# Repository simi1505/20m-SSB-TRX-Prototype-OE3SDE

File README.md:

# 20m-SSB-TRX-Prototype-OE3SDE
Prototype on a 20m SSB TRX for ham radio by OE3SDE.

## Block Diagram

**Figure 1**: Block diagram of 20m SSB TRX.

## Frequency Spectrum

**Figure 2**: Frequency spectrum of 20m SSB TRX.

## Result

**Figure 3**: Result of 20m SSB TRX prototype.

**Figure 4**: Result of 20m SSB TRX prototype.

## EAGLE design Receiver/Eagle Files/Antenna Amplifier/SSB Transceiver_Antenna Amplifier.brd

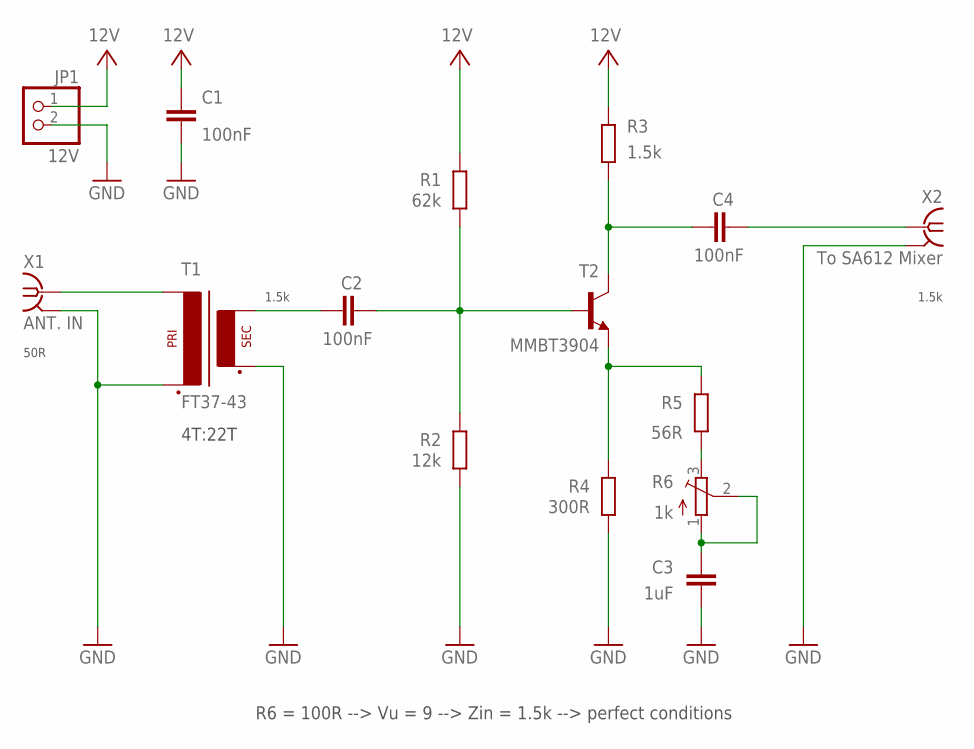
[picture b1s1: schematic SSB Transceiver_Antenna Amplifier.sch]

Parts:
C1, C2, C4: 100nF; C0805
C3: 1uF; C0805
JP1: 12V; 1X02
R1: 62k; R0805
R2: 12k; R0805
R3: 1.5k; R0805
R4: 300R; R0805
R5: 56R; R0805
R6: 1k; 3223G
T1: FT37-43; FT37-43SMD
T2: MMBT3904; SOT23-BEC
X1: ANT. IN; J502-ND-142-0711-821/826
X2: To SA612 Mixer; J502-ND-142-0711-821/826

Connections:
GND: C1.1, C3.1, JP1.2, R2.2, R4.2, T1.P$2 (P2), T1.S$2 (S2), X1.G@1 (2), X1.G@2 (2), X1.G@3 (2), X1.G@4 (2), X2.G@1 (2), X2.G@2 (2), X2.G@3 (2), X2.G@4 (2)
unnamed: R4.1, R5.1, T2.E
unnamed: C3.2, R6.1 (A), R6.2 (S)
unnamed: C4.1, R3.2, T2.C
unnamed: T1.P$1 (P1), X1.1
unnamed: C2.2, R1.2, R2.1, T2.B
unnamed: C4.2, X2.1
unnamed: C2.1, T1.S$1 (S1)
unnamed: R5.2, R6.3 (E)
VCC: C1.2, JP1.1, R1.1, R3.1

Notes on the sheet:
50R
1.5k
4T:22T
R6 = 100R --> Vu = 9 --> Zin = 1.5k --> perfect conditions

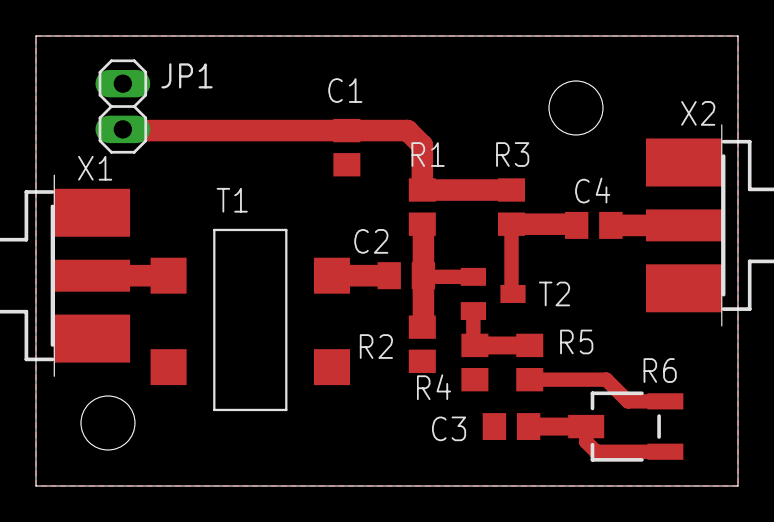
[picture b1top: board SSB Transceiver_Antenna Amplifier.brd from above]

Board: 2 copper layers, 39.0 x 25.0 mm, 15 parts (0 on the bottom side), 10 nets.

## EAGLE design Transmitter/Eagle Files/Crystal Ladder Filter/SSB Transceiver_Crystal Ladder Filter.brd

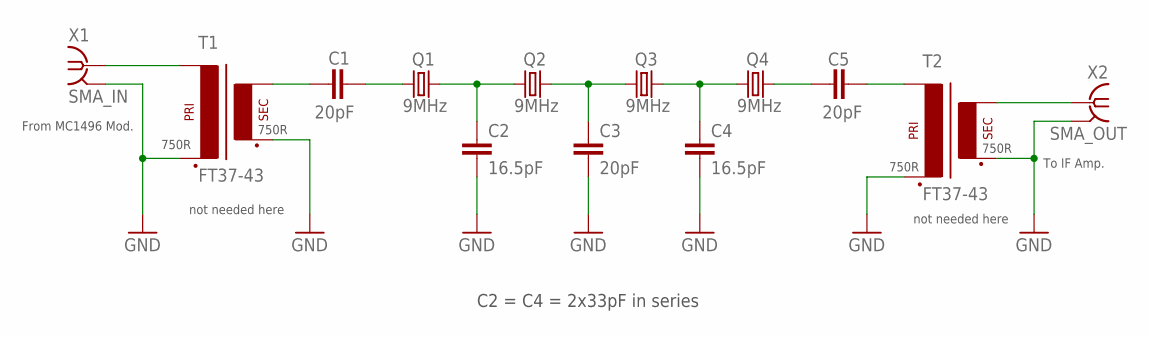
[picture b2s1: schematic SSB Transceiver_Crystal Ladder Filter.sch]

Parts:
C1, C3, C5: 20pF; C0805
C2, C4: 16.5pF; C0805
Q1, Q2, Q3, Q4: 9MHz; HC49/S
T1, T2: FT37-43; FT37-43SMD
X1: SMA_IN; J502-ND-142-0711-821/826
X2: SMA_OUT; J502-ND-142-0711-821/826

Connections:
GND: C2.2, C3.2, C4.2, T1.P$2 (P2), T1.S$2 (S2), T2.P$2 (P2), T2.S$2 (S2), X1.G@1 (2), X1.G@2 (2), X1.G@3 (2), X1.G@4 (2), X2.G@1 (2), X2.G@2 (2), X2.G@3 (2), X2.G@4 (2)
unnamed: C5.2, T2.P$1 (P1)
unnamed: T2.S$1 (S1), X2.1
unnamed: C1.1, T1.S$1 (S1)
unnamed: T1.P$1 (P1), X1.1
unnamed: C1.2, Q1.1
unnamed: C2.1, Q1.2, Q2.1
unnamed: C3.1, Q2.2, Q3.1
unnamed: C4.1, Q3.2, Q4.1
unnamed: C5.1, Q4.2

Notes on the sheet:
not needed here
750R
C2 = C4 = 2x33pF in series
From MC1496 Mod.
To IF Amp.

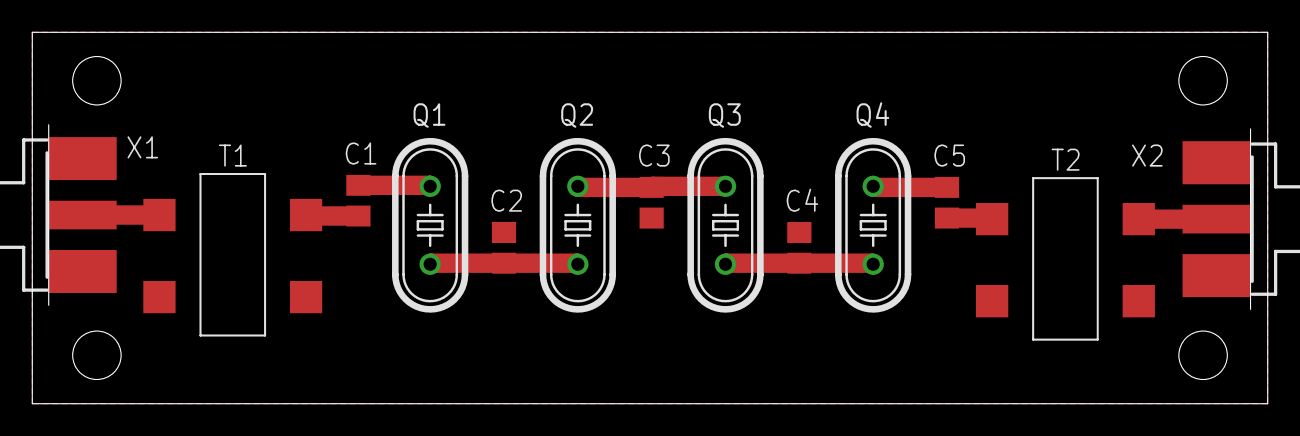
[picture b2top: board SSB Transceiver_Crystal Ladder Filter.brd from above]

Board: 2 copper layers, 76.5 x 23.0 mm, 13 parts (0 on the bottom side), 10 nets.

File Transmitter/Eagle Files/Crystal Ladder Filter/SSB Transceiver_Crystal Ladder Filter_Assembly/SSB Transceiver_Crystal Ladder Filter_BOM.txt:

Partlist exported from E:/Simon Dorrer/DIY Projekte/Amateurfunkprojekte/SSB Transceiver/Transmitter/Eagle Files/Crystal Ladder Filter/SSB Transceiver_Crystal Ladder Filter.sch at 13/01/2020 09:06

Qty Value   Device               Package                  Parts          Description                                           MF                 MPN          OC_FARNELL OC_NEWARK POPULARITY SPICEPREFIX
2   16.5pF  C-EUC0805            C0805                    C2, C4         CAPACITOR, European symbol                                                                                 88         C          
3   20pF    C-EUC0805            C0805                    C1, C3, C5     CAPACITOR, European symbol                                                                                 88         C          
4   9MHz    CRYSTALHC49S         HC49/S                   Q1, Q2, Q3, Q4 CRYSTAL                                                                               1667008    unknown                         
2   FT37-43 FT37-43              FT37-43SMD               T1, T2                                                                                                                                          
1   SMA_IN  SMA-142-0711-821/826 J502-ND-142-0711-821/826 X1             SMA 50 Ohm End Launch Jack Receptacle - Round Contact JOHNSON COMPONENTS 142-0711-821 1019328    16F3627                         
1   SMA_OUT SMA-142-0711-821/826 J502-ND-142-0711-821/826 X2             SMA 50 Ohm End Launch Jack Receptacle - Round Contact JOHNSON COMPONENTS 142-0711-821 1019328    16F3627

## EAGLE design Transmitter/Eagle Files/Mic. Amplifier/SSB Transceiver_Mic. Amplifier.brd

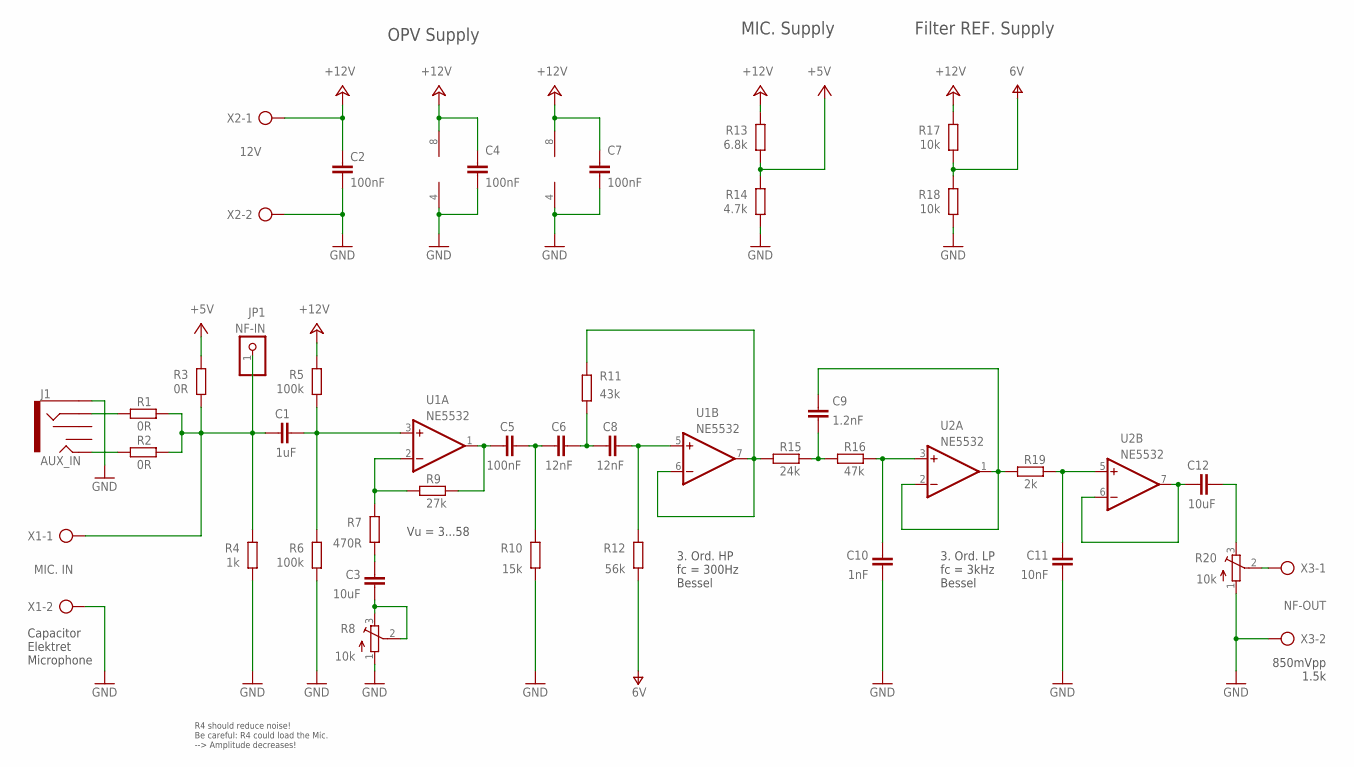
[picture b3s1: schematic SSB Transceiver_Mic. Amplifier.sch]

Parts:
C1: 1uF; C0805
C2, C4, C5, C7: 100nF; C0805
C3, C12: 10uF; C0805
C6, C8: 12nF; C0805
C9: 1.2nF; C0805
C10: 1nF; C0805
C11: 10nF; C0805
J1: AUX_IN; AUDIO-JACK
JP1: NF-IN; 1X01
R1, R2, R3: 0R; R0805
R4: 1k; R0805
R5, R6: 100k; R0805
R7: 470R; R0805
R8, R20: 10k; 3223G
R9: 27k; R0805
R10: 15k; R0805
R11: 43k; R0805
R12: 56k; R0805
R13: 6.8k; R0805
R14: 4.7k; R0805
R15: 24k; R0805
R16: 47k; R0805
R17, R18: 10k; R0805
R19: 2k; R0805
U1, U2: NE5532; SO08
X1: MIC. IN; AK550/2
X2: 12V; AK550/2
X3: NF-OUT; AK550/2

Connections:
+5V: R3.1, R13.2, R14.1
+24V: C2.2, C4.2, C7.2, R5.1, R13.1, R17.1, U1.8 (V+), U2.8 (V+), X2.1
GND: C2.1, C4.1, C7.1, C10.1, C11.1, J1.SLEEVE, R4.2, R6.2, R8.1 (A), R10.2, R14.2, R18.2, R20.1 (A), U1.4 (V-), U2.4 (V-), X1.2, X2.2, X3.2
unnamed: J1.RING, R1.2
unnamed: J1.TIP, R2.2
unnamed: R7.1, R9.1, U1.2 (-IN)
unnamed: C1.1, JP1.1, R1.1, R2.1, R3.2, R4.1, X1.1
unnamed: C1.2, R5.2, R6.1, U1.3 (+IN)
unnamed: C3.2, R7.2
unnamed: C3.1, R8.2 (S), R8.3 (E)
unnamed: C5.1, R9.2, U1.1 (OUT)
unnamed: C5.2, C6.1, R10.1
unnamed: C12.1, U2.6 (-IN), U2.7 (OUT)
unnamed: R20.2 (S), X3.1
unnamed: C12.2, R20.3 (E)
unnamed: R11.1, R15.2, U1.6 (-IN), U1.7 (OUT)
unnamed: C6.2, C8.1, R11.2
unnamed: C8.2, R12.1, U1.5 (+IN)
unnamed: C9.1, R15.1, R16.2
unnamed: C10.2, R16.1, U2.3 (+IN)
unnamed: C9.2, R19.2, U2.1 (OUT), U2.2 (-IN)
unnamed: C11.2, R19.1, U2.5 (+IN)
V+: R12.2, R17.2, R18.1

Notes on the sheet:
Capacitor Elektret Microphone
OPV Supply
MIC. Supply
Filter REF. Supply
Vu = 3...58
3. Ord. HP fc = 300Hz Bessel
3. Ord. LP fc = 3kHz Bessel
850mVpp 1.5k
R4 should reduce noise! Be careful: R4 could load the Mic. --> Amplitude decreases!

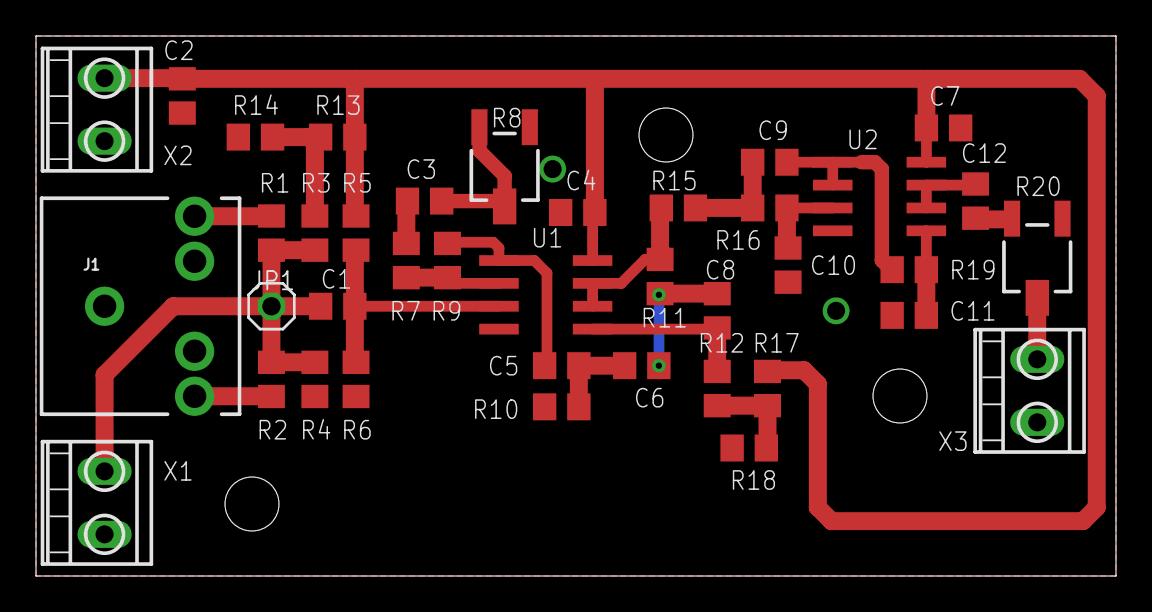
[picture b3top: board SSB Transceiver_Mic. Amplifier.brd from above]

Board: 2 copper layers, 60.0 x 30.0 mm, 39 parts (0 on the bottom side), 23 nets.

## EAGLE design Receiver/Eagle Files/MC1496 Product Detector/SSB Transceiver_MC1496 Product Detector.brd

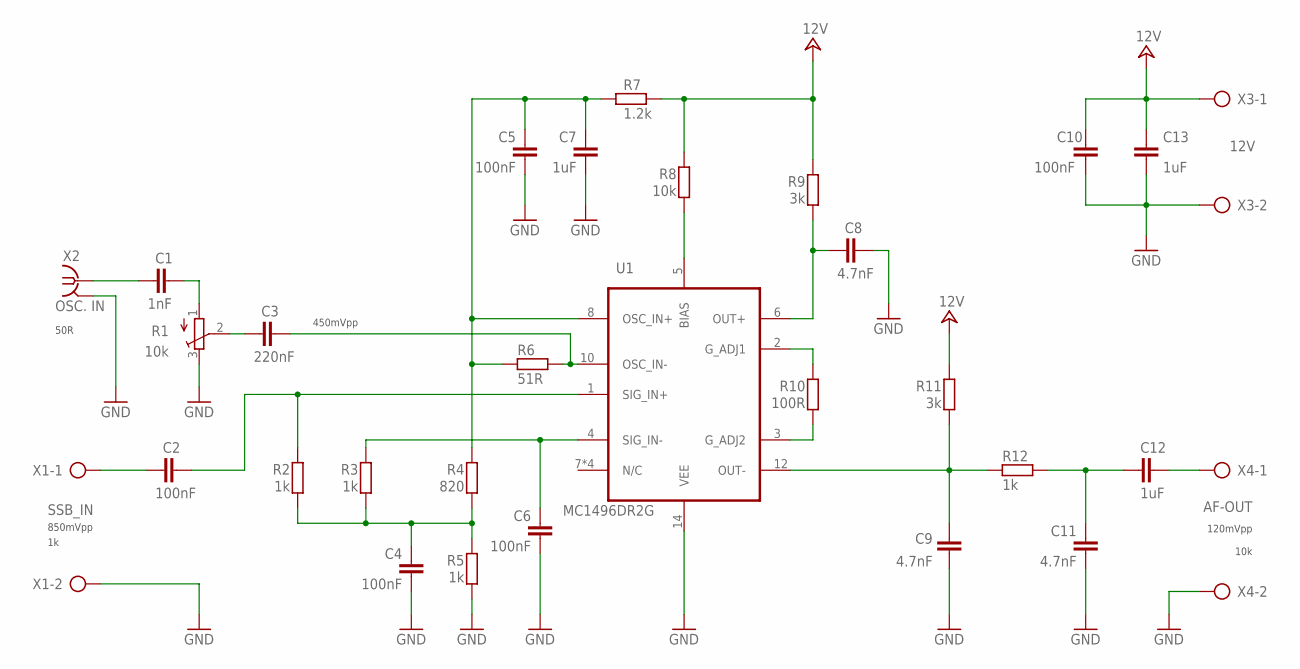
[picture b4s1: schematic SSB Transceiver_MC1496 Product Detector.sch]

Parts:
C1: 1nF; C0805
C2, C4, C5, C6, C10: 100nF; C0805
C3: 220nF; C0805
C7, C12, C13: 1uF; C0805
C8, C9, C11: 4.7nF; C0805
R1: 10k; 3223G
R2, R3, R5, R12: 1k; R0805
R4: 820; R0805
R6: 51R; R0805
R7: 1.2k; R0805
R8: 10k; R0805
R9, R11: 3k; R0805
R10: 100R; R0805
U1: MC1496DR2G; SOIC127P600X175-14N
X1: SSB_IN; AK300/2
X2: OSC. IN; J502-ND-142-0711-821/826
X3: 12V; AK300/2
X4: AF-OUT; AK300/2

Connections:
+24V: C10.2, C13.2, R7.2, R8.1, R9.1, R11.1, X3.1
GND: C4.1, C5.1, C6.1, C7.1, C8.1, C9.1, C10.1, C11.1, C13.1, R1.3 (E), R5.1, U1.14 (VEE), X1.2, X2.G@1 (2), X2.G@2 (2), X2.G@3 (2), X2.G@4 (2), X3.2, X4.2
unnamed: C1.1, X2.1
unnamed: C12.2, X4.1
unnamed: C1.2, R1.1 (A)
unnamed: C3.1, R1.2 (S)
unnamed: C8.2, R9.2, U1.6 (OUT+)
unnamed: C9.2, R11.2, R12.1, U1.12 (OUT-)
unnamed: C11.2, C12.1, R12.2
unnamed: R10.2, U1.3 (G_ADJ2)
unnamed: R10.1, U1.2 (G_ADJ1)
unnamed: C3.2, R6.2, U1.10 (OSC_IN-)
unnamed: R8.2, U1.5 (BIAS)
unnamed: C6.2, R3.1, U1.4 (SIG_IN-)
unnamed: C2.2, R2.2, U1.1 (SIG_IN+)
unnamed: C4.2, R2.1, R3.2, R4.1, R5.2
unnamed: C2.1, X1.1
unnamed: C5.2, C7.2, R4.2, R6.1, R7.1, U1.8 (OSC_IN+)

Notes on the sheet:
10k
120mVpp
50R
450mVpp
850mVpp

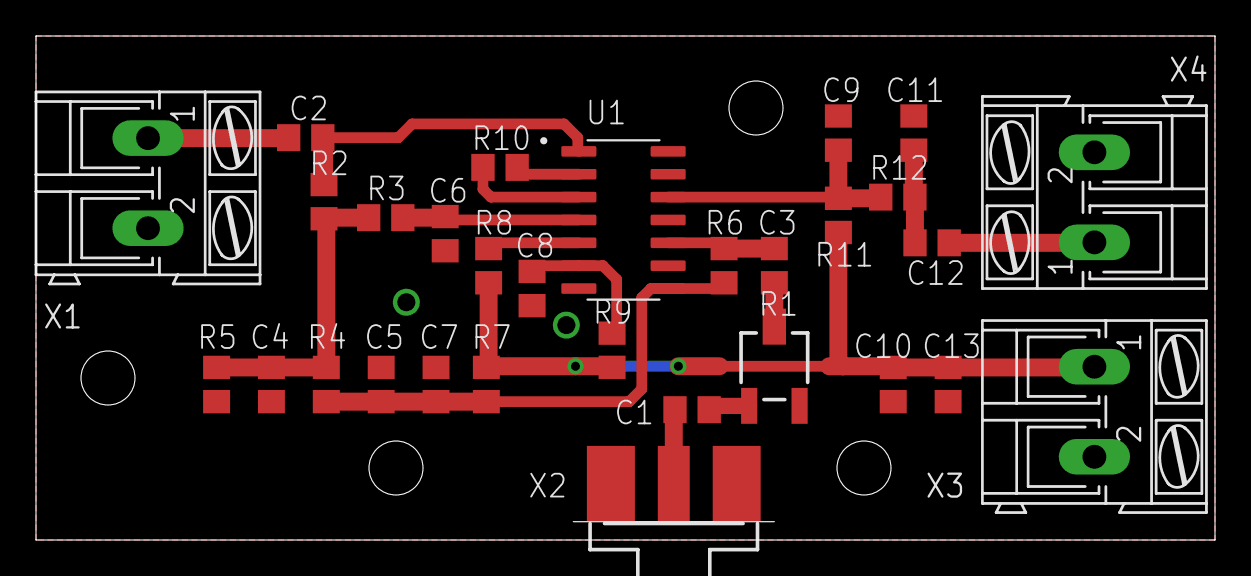
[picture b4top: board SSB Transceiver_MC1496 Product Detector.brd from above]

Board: 2 copper layers, 65.5 x 28.0 mm, 30 parts (0 on the bottom side), 18 nets.

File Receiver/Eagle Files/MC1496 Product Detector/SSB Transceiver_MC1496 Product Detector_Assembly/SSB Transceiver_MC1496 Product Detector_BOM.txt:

Partlist exported from E:/Simon Dorrer/DIY Projekte/Amateurfunkprojekte/SSB Transceiver/Receiver/Eagle Files/MC1496 Product Detector/SSB Transceiver_MC1496 Product Detector.sch at 12/01/2020 20:46

Qty Value      Device               Package                  Parts               Description                                           AVAILABILITY DESCRIPTION                                     MF                 MP         MPN          OC_FARNELL OC_NEWARK PACKAGE                  POPULARITY PRICE SPICEPREFIX
1   1.2k       R-EU_R0805           R0805                    R7                  RESISTOR, European symbol                                                                                                                                                                                   86               R          
1   100R       R-EU_R0805           R0805                    R10                 RESISTOR, European symbol                                                                                                                                                                                   86               R          
5   100nF      C-EUC0805            C0805                    C2, C4, C5, C6, C10 CAPACITOR, European symbol                                                                                                                                                                                  88               C          
1   10k        R-EU_R0805           R0805                    R8                  RESISTOR, European symbol                                                                                                                                                                                   86               R          
1   10k        TRIM_EU-3223G        3223G                    R1                  POTENTIOMETER                                                                                                                                                                                                                           
1   12V        AK300/2              AK300/2                  X3                  CONNECTOR                                                                                                                                                     unknown    unknown                                                        
4   1k         R-EU_R0805           R0805                    R2, R3, R5, R12     RESISTOR, European symbol                                                                                                                                                                                   86               R          
1   1nF        C-EUC0805            C0805                    C1                  CAPACITOR, European symbol                                                                                                                                                                                  88               C          
3   1uF        C-EUC0805            C0805                    C7, C12, C13        CAPACITOR, European symbol                                                                                                                                                                                  88               C          
1   220nF      C-EUC0805            C0805                    C3                  CAPACITOR, European symbol                                                                                                                                                                                  88               C          
2   3k         R-EU_R0805           R0805                    R9, R11             RESISTOR, European symbol                                                                                                                                                                                   86               R          
3   4.7nF      C-EUC0805            C0805                    C8, C9, C11         CAPACITOR, European symbol                                                                                                                                                                                  88               C          
1   51R        R-EU_R0805           R0805                    R6                  RESISTOR, European symbol                                                                                                                                                                                   86               R          
1   820        R-EU_R0805           R0805                    R4                  RESISTOR, European symbol                                                                                                                                                                                   86               R          
1   AF-OUT     AK300/2              AK300/2                  X4                  CONNECTOR                                                                                                                                                     unknown    unknown                                                        
1   MC1496DR2G MC1496DR2G           SOIC127P600X175-14N      U1                                                                        Unavailable   RF IC Modulator/Demodulator FM 300MHz 14-SOIC  ON Semiconductor   MC1496DR2G                                   SOIC-14 ON Semiconductor            None             
1   OSC. IN    SMA-142-0711-821/826 J502-ND-142-0711-821/826 X2                  SMA 50 Ohm End Launch Jack Receptacle - Round Contact                                                              JOHNSON COMPONENTS            142-0711-821 1019328    16F3627                                                        
1   SSB_IN     AK300/2              AK300/2                  X1                  CONNECTOR                                                                                                                                                     unknown    unknown

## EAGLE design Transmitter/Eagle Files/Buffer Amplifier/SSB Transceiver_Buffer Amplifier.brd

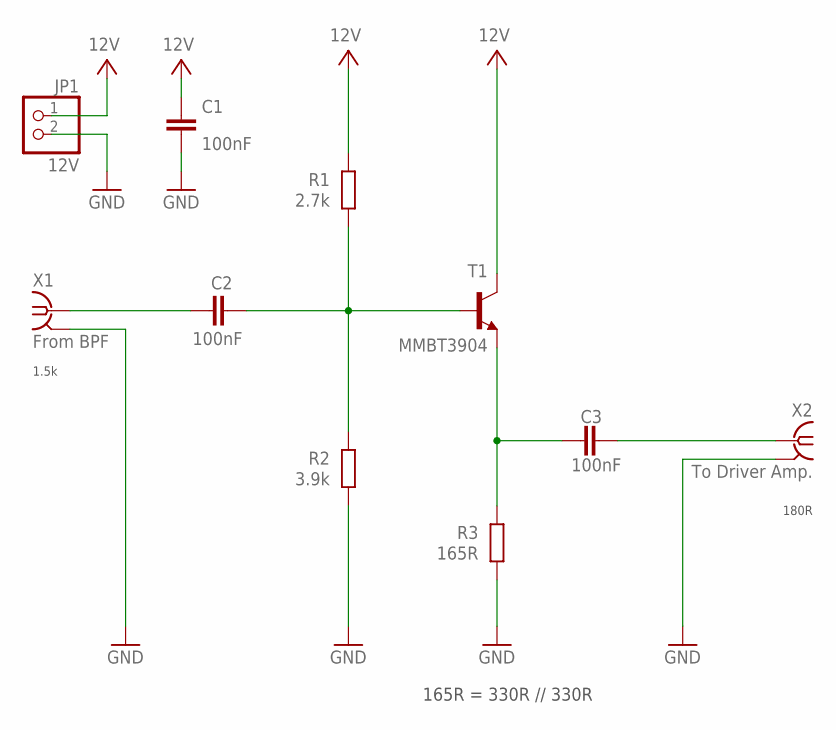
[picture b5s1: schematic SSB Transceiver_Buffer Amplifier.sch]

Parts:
C1, C2, C3: 100nF; C0805
JP1: 12V; 1X02
R1: 2.7k; R0805
R2: 3.9k; R0805
R3: 165R; R0805
T1: MMBT3904; SOT23-BEC
X1: From BPF; J502-ND-142-0711-821/826
X2: To Driver Amp.; J502-ND-142-0711-821/826

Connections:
GND: C1.1, JP1.2, R2.2, R3.2, X1.G@1 (GND), X1.G@2 (GND), X1.G@3 (GND), X1.G@4 (GND), X2.G@1 (GND), X2.G@2 (GND), X2.G@3 (GND), X2.G@4 (GND)
unnamed: C3.2, R3.1, T1.E
unnamed: C3.1, X2.1 (RF)
unnamed: C2.2, R1.2, R2.1, T1.B
unnamed: C2.1, X1.1 (RF)
VCC: C1.2, JP1.1, R1.1, T1.C

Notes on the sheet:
1.5k
180R
165R = 330R // 330R

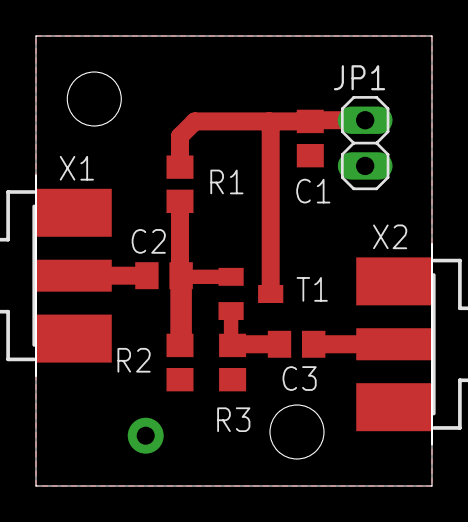
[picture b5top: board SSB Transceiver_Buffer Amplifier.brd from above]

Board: 2 copper layers, 22.0 x 25.0 mm, 10 parts (0 on the bottom side), 6 nets.

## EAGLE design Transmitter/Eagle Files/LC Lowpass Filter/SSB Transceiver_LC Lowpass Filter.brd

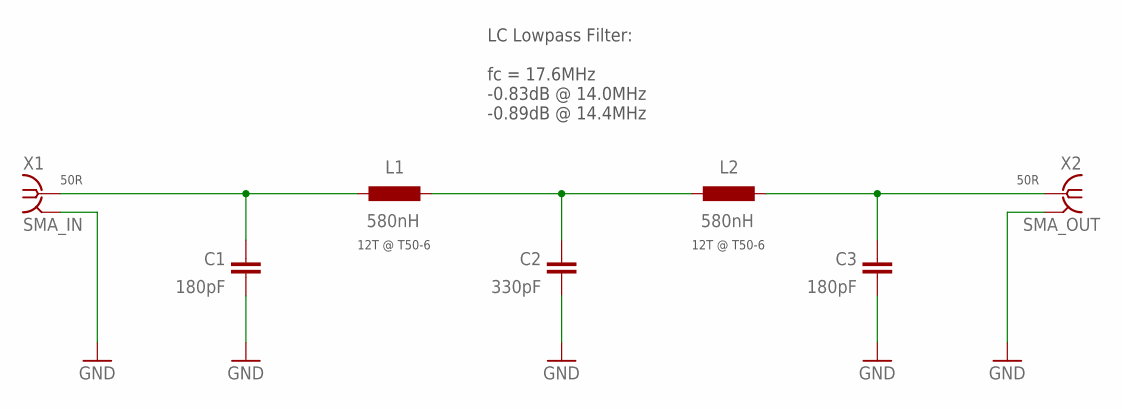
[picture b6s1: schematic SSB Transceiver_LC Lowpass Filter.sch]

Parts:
C1, C3: 180pF; C0805
C2: 330pF; C0805
L1, L2: 580nH; T50-6SMD
X1: SMA_IN; J502-ND-142-0711-821/826
X2: SMA_OUT; J502-ND-142-0711-821/826

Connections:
GND: C1.1, C2.1, C3.1, X1.G@1 (2), X1.G@2 (2), X1.G@3 (2), X1.G@4 (2), X2.G@1 (2), X2.G@2 (2), X2.G@3 (2), X2.G@4 (2)
unnamed: C2.2, L1.P$2 (2), L2.P$1 (1)
unnamed: C3.2, L2.P$2 (2), X2.1
unnamed: C1.2, L1.P$1 (1), X1.1

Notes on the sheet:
50R
LC Lowpass Filter: fc = 17.6MHz -0.83dB @ 14.0MHz -0.89dB @ 14.4MHz
12T @ T50-6

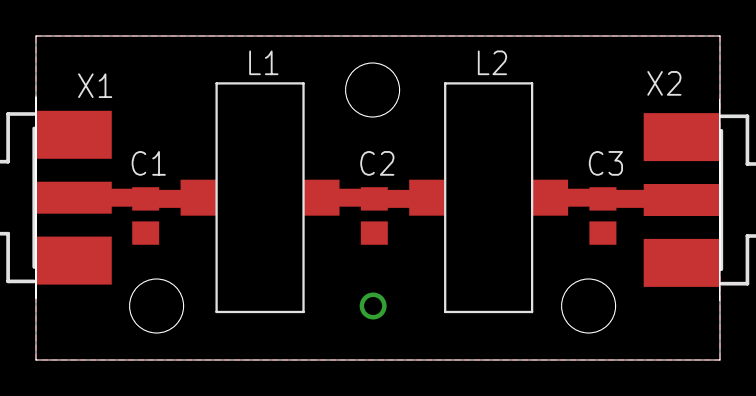
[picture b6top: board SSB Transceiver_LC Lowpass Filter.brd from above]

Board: 2 copper layers, 38.0 x 18.0 mm, 7 parts (0 on the bottom side), 4 nets.

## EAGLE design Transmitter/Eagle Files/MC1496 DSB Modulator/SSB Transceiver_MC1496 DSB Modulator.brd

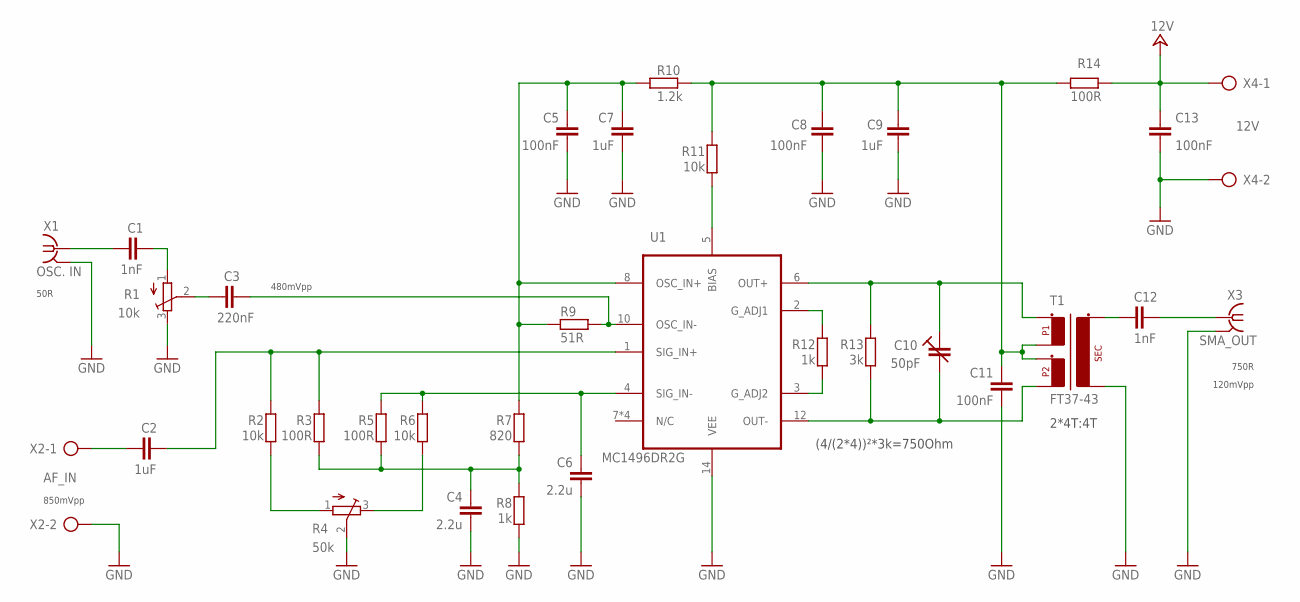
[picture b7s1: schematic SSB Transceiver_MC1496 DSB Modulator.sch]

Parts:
C1, C12: 1nF; C0805
C2, C7, C9: 1uF; C0805
C3: 220nF; C0805
C4, C6: 2.2u; C0805
C5, C8, C11, C13: 100nF; C0805
C10: 50pF; VARIABLECAP-SMD
R1: 10k; 3223G
R2, R6, R11: 10k; R0805
R3, R5, R14: 100R; R0805
R4: 50k; 3223G
R7: 820; R0805
R8, R12: 1k; R0805
R9: 51R; R0805
R10: 1.2k; R0805
R13: 3k; R0805
T1: FT37-43; FT37-43CENTERTAPSMD
U1: MC1496DR2G; SOIC127P600X175-14N
X1: OSC. IN; J502-ND-142-0711-821/826
X2: AF_IN; AK300/2
X3: SMA_OUT; J502-ND-142-0711-821/826
X4: 12V; AK300/2

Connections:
+24V: C13.2, R14.2, X4.1
GND: C4.1, C5.1, C6.1, C7.1, C8.1, C9.1, C11.1, C13.1, R1.3 (E), R4.2 (S), R8.1, T1.S$2 (S2), U1.14 (VEE), X1.G@1 (2), X1.G@2 (2), X1.G@3 (2), X1.G@4 (2), X2.2, X3.G@1 (2), X3.G@2 (2), X3.G@3 (2), X3.G@4 (2), X4.2
unnamed: C1.1, X1.1
unnamed: C12.2, X3.1
unnamed: C1.2, R1.1 (A)
unnamed: C3.1, R1.2 (S)
unnamed: C8.2, C9.2, C11.2, R10.2, R11.1, R14.1, T1.P$2 (P1_2), T1.P$3 (P2_1)
unnamed: C12.1, T1.S$1 (S1)
unnamed: C10.P$1 (E), R13.1, T1.P$1 (P1_1), U1.6 (OUT+)
unnamed: C10.P$2 (A), R13.2, T1.P$4 (P2_2), U1.12 (OUT-)
unnamed: R12.2, U1.3 (G_ADJ2)
unnamed: R12.1, U1.2 (G_ADJ1)
unnamed: C3.2, R9.2, U1.10 (OSC_IN-)
unnamed: R11.2, U1.5 (BIAS)
unnamed: R2.1, R4.1 (A)
unnamed: R4.3 (E), R6.2
unnamed: C6.2, R5.2, R6.1, U1.4 (SIG_IN-)
unnamed: C2.2, R2.2, R3.2, U1.1 (SIG_IN+)
unnamed: C4.2, R3.1, R5.1, R7.1, R8.2
unnamed: C2.1, X2.1
unnamed: C5.2, C7.2, R7.2, R9.1, R10.1, U1.8 (OSC_IN+)

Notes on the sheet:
750R
120mVpp
50R
480mVpp
850mVpp
(4/(2*4))²*3k=750Ohm
2*4T:4T

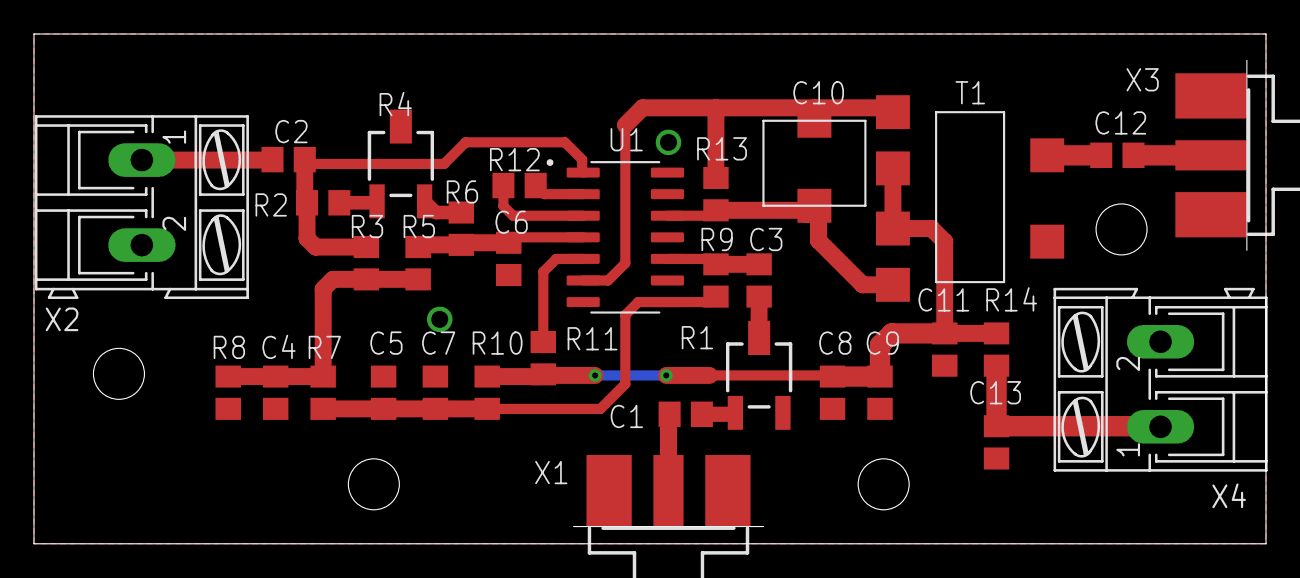
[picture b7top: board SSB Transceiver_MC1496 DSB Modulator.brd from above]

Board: 2 copper layers, 72.5 x 30.0 mm, 33 parts (0 on the bottom side), 21 nets.

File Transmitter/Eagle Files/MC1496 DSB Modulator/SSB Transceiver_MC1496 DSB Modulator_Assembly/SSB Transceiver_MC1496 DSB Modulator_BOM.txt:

Partlist exported from E:/Simon Dorrer/DIY Projekte/Amateurfunkprojekte/SSB Transceiver/Transmitter/Eagle Files/MC1496 DSB Modulator/SSB Transceiver_MC1496 DSB Modulator.sch at 12/01/2020 14:15

Qty Value      Device               Package                  Parts            Description                                           AVAILABILITY DESCRIPTION                                     MF                 MP         MPN          OC_FARNELL OC_NEWARK PACKAGE                  POPULARITY PRICE SPICEPREFIX
1   1.2k       R-EU_R0805           R0805                    R10              RESISTOR, European symbol                                                                                                                                                                                   86               R          
3   100R       R-EU_R0805           R0805                    R3, R5, R14      RESISTOR, European symbol                                                                                                                                                                                   86               R          
4   100nF      C-EUC0805            C0805                    C5, C8, C11, C13 CAPACITOR, European symbol                                                                                                                                                                                  88               C          
3   10k        R-EU_R0805           R0805                    R2, R6, R11      RESISTOR, European symbol                                                                                                                                                                                   86               R          
1   10k        TRIM_EU-3223G        3223G                    R1               POTENTIOMETER                                                                                                                                                                                                                           
1   12V        AK300/2              AK300/2                  X4               CONNECTOR                                                                                                                                                     unknown    unknown                                                        
2   1k         R-EU_R0805           R0805                    R8, R12          RESISTOR, European symbol                                                                                                                                                                                   86               R          
2   1nF        C-EUC0805            C0805                    C1, C12          CAPACITOR, European symbol                                                                                                                                                                                  88               C          
3   1uF        C-EUC0805            C0805                    C2, C7, C9       CAPACITOR, European symbol                                                                                                                                                                                  88               C          
2   2.2u       C-EUC0805            C0805                    C4, C6           CAPACITOR, European symbol                                                                                                                                                                                  88               C          
1   220nF      C-EUC0805            C0805                    C3               CAPACITOR, European symbol                                                                                                                                                                                  88               C          
1   3k       R-EU_R0805           R0805                    R13              RESISTOR, European symbol                                                                                                                                                                                   86               R          
1   50k        TRIM_EU-3223G        3223G                    R4               POTENTIOMETER                                                                                                                                                                                                                           
1   50pF       VARIABLECAP          VARIABLECAP-SMD          C10                                                                                                                                                                                                                                                      
1   51R        R-EU_R0805           R0805                    R9               RESISTOR, European symbol                                                                                                                                                                                   86               R          
1   820        R-EU_R0805           R0805                    R7               RESISTOR, European symbol                                                                                                                                                                                   86               R          
1   AF_IN      AK300/2              AK300/2                  X2               CONNECTOR                                                                                                                                                     unknown    unknown                                                        
1   FT37-43    FT37-43CENTERTAP     FT37-43CENTERTAPSMD      T1                                                                                                                                                                                                                                                       
1   MC1496DR2G MC1496DR2G           SOIC127P600X175-14N      U1                                                                     Unavailable   RF IC Modulator/Demodulator FM 300MHz 14-SOIC  ON Semiconductor   MC1496DR2G                                   SOIC-14 ON Semiconductor            None             
1   OSC. IN    SMA-142-0711-821/826 J502-ND-142-0711-821/826 X1               SMA 50 Ohm End Launch Jack Receptacle - Round Contact                                                              JOHNSON COMPONENTS            142-0711-821 1019328    16F3627                                                        
1   SMA_OUT    SMA-142-0711-821/826 J502-ND-142-0711-821/826 X3               SMA 50 Ohm End Launch Jack Receptacle - Round Contact                                                              JOHNSON COMPONENTS            142-0711-821 1019328    16F3627

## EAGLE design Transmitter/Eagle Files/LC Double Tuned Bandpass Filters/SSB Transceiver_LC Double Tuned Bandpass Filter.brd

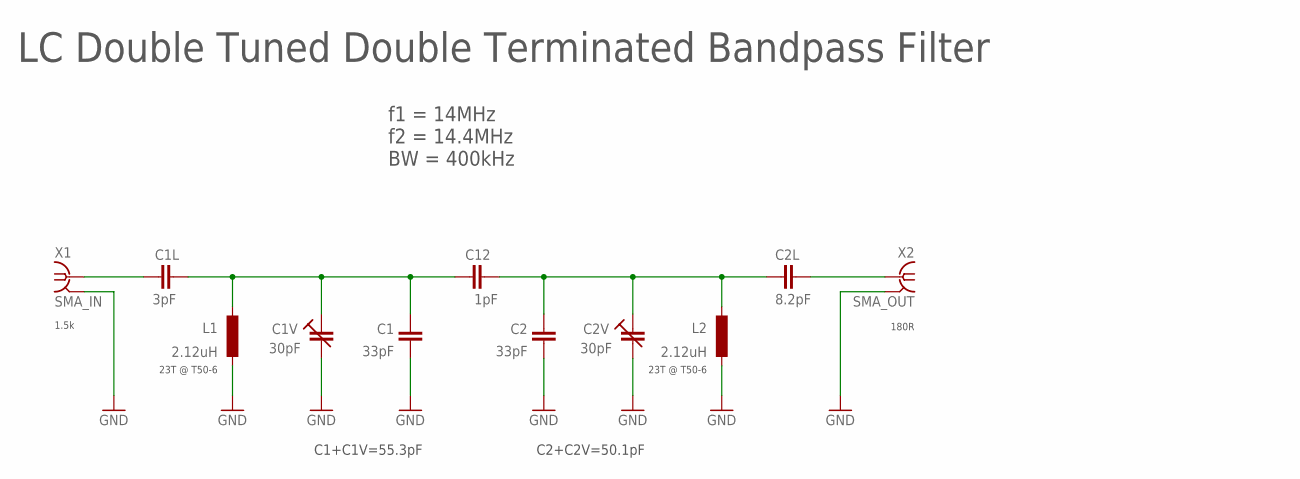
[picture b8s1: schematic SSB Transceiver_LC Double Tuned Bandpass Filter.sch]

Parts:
C1, C2: 33pF; C0805
C1L: 3pF; C0805
C1V, C2V: 30pF; VARIABLECAP-SMD
C2L: 8.2pF; C0805
C12: 1pF; C0805
L1, L2: 2.12uH; T50-6SMD
X1: SMA_IN; J502-ND-142-0711-821/826
X2: SMA_OUT; J502-ND-142-0711-821/826

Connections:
GND: C1.1, C1V.P$2 (A), C2.1, C2V.P$2 (A), L1.P$2 (2), L2.P$2 (2), X1.G@1 (2), X1.G@2 (2), X1.G@3 (2), X1.G@4 (2), X2.G@1 (2), X2.G@2 (2), X2.G@3 (2), X2.G@4 (2)
unnamed: C1.2, C1L.2, C1V.P$1 (E), C12.1, L1.P$1 (1)
unnamed: C2.2, C2L.2, C2V.P$1 (E), C12.2, L2.P$1 (1)
unnamed: C2L.1, X2.1
unnamed: C1L.1, X1.1

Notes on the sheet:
1.5k
180R
C1+C1V=55.3pF
C2+C2V=50.1pF
23T @ T50-6
f1 = 14MHz f2 = 14.4MHz BW = 400kHz
LC Double Tuned Double Terminated Bandpass Filter

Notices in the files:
parts and their libraries:
SparkFun-Connectors: Licensing: Creative Commons ShareAlike 4.0 International - https://creativecommons.org/licenses/by-sa/4.0
